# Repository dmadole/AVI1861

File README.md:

# AVI1861

Note: I have found in testing that a 74HC4040 works consistently well where the CD4040 previously specified may require parts to be hand-picked, so I have changed the BOM to the HCMOS part. I have also updated the FRAME PLD code to output a 8-line-wide vertical sync pulse instead of 16 lines as, while this is different than the CDP1861, it does improve display quality on some analog monitors and I don't think hurts anything. I am calling this revision B1 as there is no circuit board change.

Note: I have updated the design to revision B, which corrects an issue in the original STG1861 in which the clock input to the shift register is the opposite polarity of the CDP1861. In most circuits it doesn't matter but in certain cases and with older CDP1802 processors, it causes display anomalies, and this revision corrects that.

This is an update of the [AVI1861](http://www.cosmacvip.com/avi1861/avi1861.html) which is a drop-in replacement for the obsolete RCA [CDP1861](http://www.cosmacelf.com/publications/data-sheets/cdp1861.pdf) video chip. While the CDP1861 was a very low-cost way to produce video, it was rather low resolution and had other severe limitations such as being tied extremely closely to the RCA1802 microprocessor. Thus, although it was used in many iconic early systems, it was never used in anything with mass-market success and went out of production in a few years and is very difficult to obtain today.

The AVI1861 itself originated in the [STG1861](http://www.sparetimegizmos.com/Hardware/Elf2K_Accessories.htm#STG1681%20Pixie%20Graphics%20Replacement) designed by Robert Armstrong for his [Elf 2000](http://www.sparetimegizmos.com/Hardware/Elf2K.htm) system around 2004 to allow users to support CDP1861 graphics even if they could not obtain an actual chip. It is a mostly compatible replacement for the CDP1861 made from a couple of 22V10 PLDs plus a counter and a shift register, comprising four chips altogether. While the STG1861 was advertised as a replacement for the CDP1861 in any application, it had a disadvantage of being much larger which could make it awkward on other machines which did not have the space and mounting holes that the Elf 2000 did.

In around 2015, Ed Keefe repackaged the STG1861 design using surface mount parts to reduce the size to that of a 24-pin DIP package so it would fit exactly in the original footprint of a CDP1861 chip. Aside from the change to SMD parts and the addition of an RC filter on the video pin to reduce the effect of a timing glitch, it was the same design as the STG1861 and used the same PLD programming. Ed called his new version the AVI1861 from the mark AVI he used for Audio Visual Imagery, his design company.

Sadly, Ed passed away in 2022. Although care has been taken to preserve and continue much of his work, the design files for the AVI1861 could not be found, so as a service to the COSMAC Elf community, I volunteered to recreate the design so that others could enjoy his idea, and this was how my version of it came about. I have corresponded with Ed many times in the past including about the AVI1861, and I have a copy of it that he built himself and gifted to me.

As I started to duplicate the design, through discussion in the [COSMAC ELF Group](https://groups.io/g/cosmacelf/) I found there were a few flaws going back to the STG1861 that made it just a slightly imperfect replacement for the CDP1861.

This started when I noted that Ed had added an RC network to the video output; when I mentioned it to the group it was revealed that was perhaps to filter out a vertical glitch that happened when the shift register was loaded. The likely reason for this is that a 74HC165 is used for the shift register, which has an asyncronous paralallel load enable, yet the load of the byte needs to be closely syncronized with the pixel clock. In the STG1861 this syncronization was done in the PLDs but due to the different propagation delays this could never be implemented perfectly. It may have also been contributed by the shift register being an HCMOS part with a faster and stronger output drive than the CMOS of the original CDP1861, complicated by the fact this feeds analog output circuitry which shows small glitches that would be irrelevant to a digital system.

I decided to correct this issue by switching to a CD4014 shift register, which has a load enable that is syncronous to the clock input, so that they will be exactly syncronized internally. Additionally, being CMOS rather than HCMOS would more closely replicate the output drive of the original chip. This change required modifying the PLD programming to invert the state of the paralell load signal, since it is the opposite of the 74HC165.

Other discussion and feedback from the group was that the AVI1861 did not work in the RCA Studio II game console, with Bob Armstrong himself suggesting that this was probably due to the RESET- input not being a Schmitt trigger like the original part. So I added a 74LVC1G17 Schmitt trigger buffer to that pin to better replicate the original behavior.

Lastly, two of the pins on the CDPO1861, INT- and DMAO- were open-drain outputs, and on the STG1861 this was accomplished by putting diodes in series with the PLD outputs so they could only drive low. Although I didn't know of any instance where this was an actual problem, as long as I was updating the design I replaced these diodes with two true open-drain gates using a 74LVC2G07 buffer.

So in the end, this is not an exact reproduction of Ed's work, but rather an improved design based on the same concept and packaging. But I am sure that is how Ed himself would have also gone about recreating it if he had to as well.

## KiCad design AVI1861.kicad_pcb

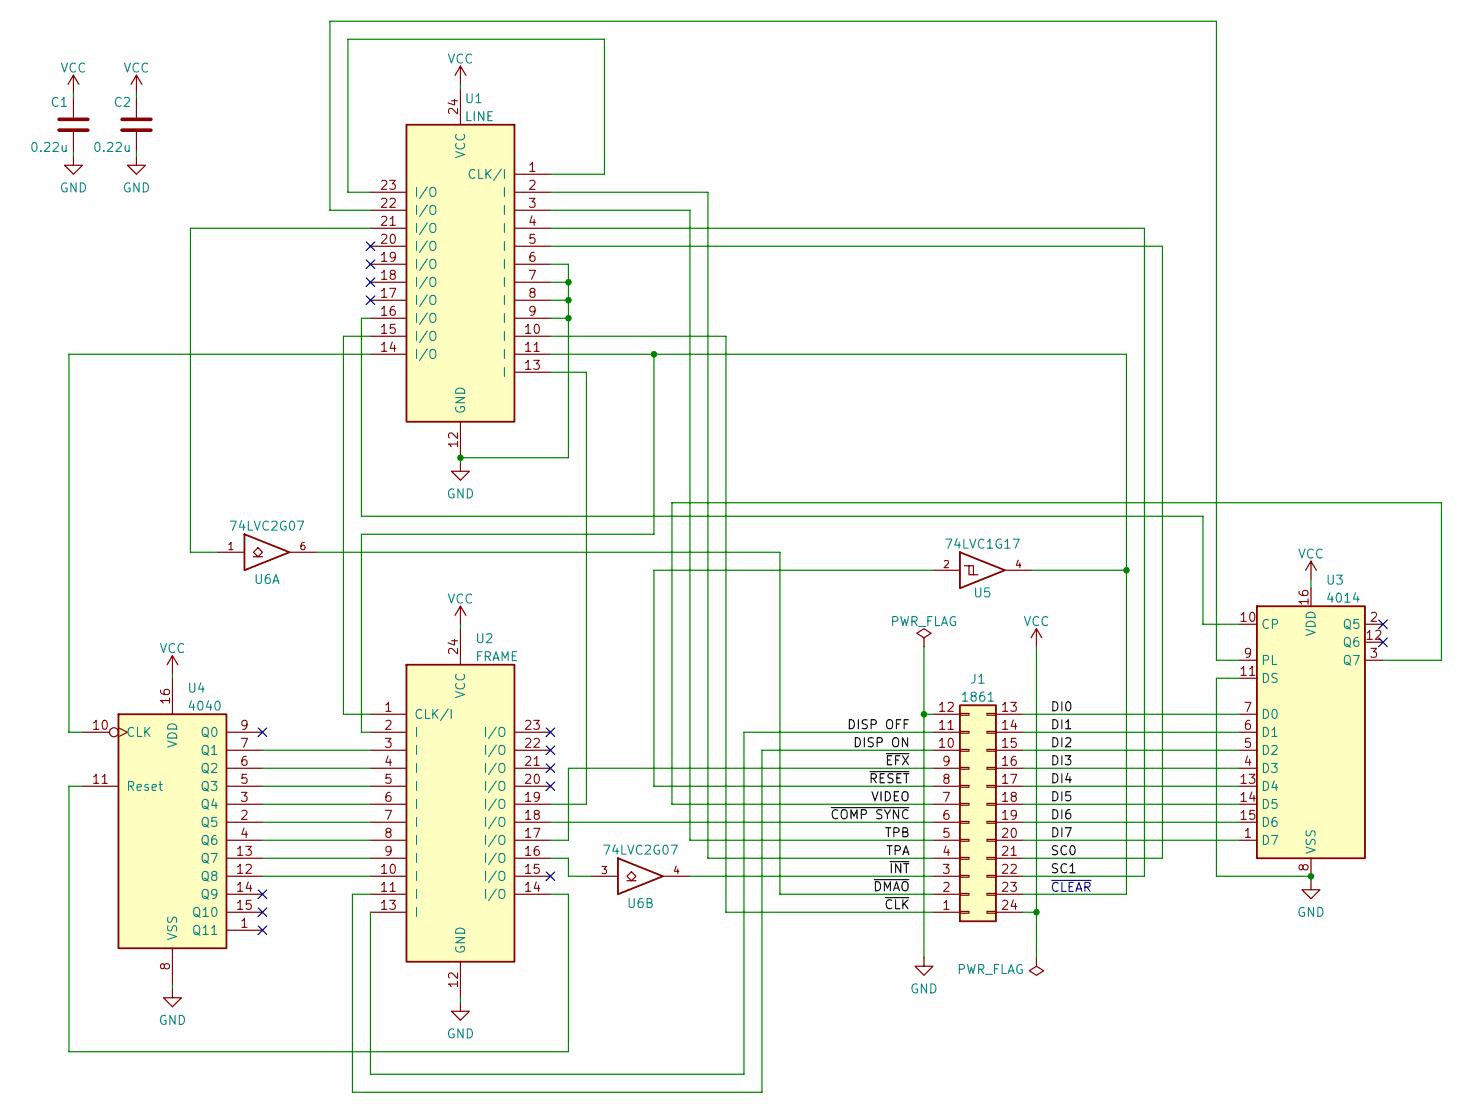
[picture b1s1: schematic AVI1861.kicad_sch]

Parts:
C1, C2: 0.22u; C_0805_2012Metric
J1: 1861; DIP-24_W15.24mm
U1: LINE; TSSOP-24_4.4x7.8mm_P0.65mm
U2: FRAME; TSSOP-24_4.4x7.8mm_P0.65mm
U3: 4014; TSSOP-16_4.4x5.0mm_P0.65mm
U4: 4040; TSSOP-16_4.4x5.0mm_P0.65mm
U5: 74LVC1G17; SOT-23-5
U6: 74LVC2G07; SOT-23-6

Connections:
/DI0: J1.13, U3.7 (D0)
/DI1: J1.14, U3.6 (D1)
/DI2: J1.15, U3.5 (D2)
/DI3: J1.16, U3.4 (D3)
/DI4: J1.17, U3.13 (D4)
/DI5: J1.18, U3.14 (D5)
/DI6: J1.19, U3.15 (D6)
/DI7: J1.20, U3.1 (D7)
/DISP OFF: J1.11, U2.13 (I)
/DISP ON: J1.10, U2.11 (I)
/SC0: J1.21, U1.5 (I)
/SC1: J1.22, U1.4 (I)
/TPA: J1.4, U1.2 (I)
/TPB: J1.5, U1.3 (I)
/VIDEO: J1.7, U3.3 (Q7)
/~CLK: J1.1, U1.10 (I)
/~COMP SYNC: J1.6, U2.18 (I/O)
/~DMAO: J1.2, U6.6
/~EFX: J1.9, U2.17 (I/O)
/~INT: J1.3, U6.4
/~RESET: J1.8, U5.2
GND: C1.2, C2.2, J1.12, U1.6 (I), U1.7 (I), U1.8 (I), U1.9 (I), U1.12 (GND), U2.12 (GND), U3.8 (VSS), U3.11 (DS), U4.8 (VSS), U5.3 (GND), U6.2 (GND)
unnamed: J1.23, U1.11 (I), U2.2 (I), U5.4
unnamed: U1.1 (CLK/I), U1.23 (I/O)
unnamed: U1.13 (I), U2.19 (I/O)
unnamed: U1.14 (I/O), U4.10 (CLK)
unnamed: U1.15 (I/O), U2.1 (CLK/I)
unnamed: U1.16 (I/O), U3.10 (CP)
unnamed: U1.21 (I/O), U6.1
unnamed: U1.22 (I/O), U3.9 (PL)
unnamed: U2.3 (I), U4.7 (Q1)
unnamed: U2.4 (I), U4.6 (Q2)
unnamed: U2.5 (I), U4.5 (Q3)
unnamed: U2.6 (I), U4.3 (Q4)
unnamed: U2.7 (I), U4.2 (Q5)
unnamed: U2.8 (I), U4.4 (Q6)
unnamed: U2.9 (I), U4.13 (Q7)
unnamed: U2.10 (I), U4.12 (Q8)
unnamed: U2.14 (I/O), U4.11 (Reset)
unnamed: U2.16 (I/O), U6.3
VCC: C1.1, C2.1, J1.24, U1.24 (VCC), U2.24 (VCC), U3.16 (VDD), U4.16 (VDD), U5.5 (VCC), U6.5 (VCC)

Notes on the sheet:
~{CLEAR}

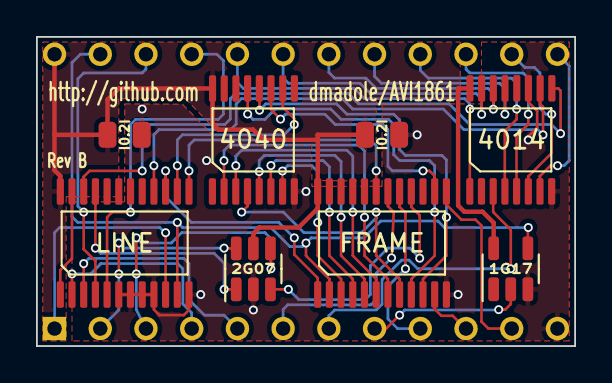
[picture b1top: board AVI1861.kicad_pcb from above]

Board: 2 copper layers, 29.9 x 17.2 mm, 9 parts (0 on the bottom side), 41 nets.

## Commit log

2024-08-01 Add photo
2024-08-07 Add note that rev b is coming
2024-08-20 Revision B changes
2024-08-20 Ad revision B note
2024-08-20 Move to release
2024-08-20 Add files via upload
    Revision B updates
2024-08-21 Create LICENSE
2024-09-13 Update with revision B1 note
2024-09-13 Change vsync to 8 lines
2024-09-13 Change 4040 to HC40404
2025-04-24 Update README.md
    Fix a couple typos H/T Bob K.
2025-11-16 Add files via upload
    Quick video of drag soldering.
